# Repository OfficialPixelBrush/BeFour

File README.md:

# BeFour
The BeFour/B4/Be4 is a simplistic 4-Bit, TTL Processor, largely inspired by the Zilog Z80 and similar architectures of the late-1970s and early-1980s, just in 4-Bit.

# Goal
It's main idea is simple. How basic can I make an instruction set, while still making it somewhat useful?
This question arose out of need. I was originally trying to make a Diode-Transistor Logic Computer entirely from Scratch, which was meant to be 4-Bit too. However, planning that monstrocity became too difficult for my current skill-set, so I decided to try anew. My main goal not being an impressive instruction set, but something simple that won't require heaps of individual Diodes and Transistors. This is also why I'll be sticking with bog-standard TTL Chips for this project.

# Architecture
This Processor is entirely 4-Bit, aside from the Address Bus, which is 8-Bit.
This allows for Addressing of up to 256 Bytes of Memory, at least as a Program. The Processor is only capable of reading a 4-Bit address for RAM access, limiting it's Memory on that front to only 16 Bytes.

For more information about the Architecture, Instruction Set, Memory Map, et cetera, please [visit the Wiki page](https://github.com/OfficialPixelBrush/BeFour/wiki).

# Emulator
The provide Emulator is accurate enough for most simple Programs, and can be compiled easily with gcc.
Pre-built Binaries can usually be found in the Releases section, although these may not always be up-to-date.

## How to use
The emulator takes two parameters. The first is the filename of whichever Binary file it's supposed to execute. The second is how many instructions it'll execute before stopping. By default, this is -1, meaning it'll stop right away.

### Windows
To execute the provided Fibonacci Program, for example, one could use `.\b4emu.exe ..\software\fibo.bin 50` to execute the Fibbonaci Program for 50 Instructions.

### Linux
Similar to Windows, just different formatting:
`./b4emu ../software/fibo.bin 50`
Outside of that, make sure the binary is set to be executable.
`chmod +x b4emu`

## Binaries
You can find all Releases in the [Releases Section](https://github.com/OfficialPixelBrush/BeFour/releases).

# License
It's been difficult finding a proper license for this thus far, especially because I don't see why anyone'd want to do much with this thing.
It's my processor, feel free to be inspired by it, but don't steal it, and don't use it commercially. I'll probably replace this with a proper license sometime soon, but if you have any deeper questions, just shoot me a message via an Issue or something.

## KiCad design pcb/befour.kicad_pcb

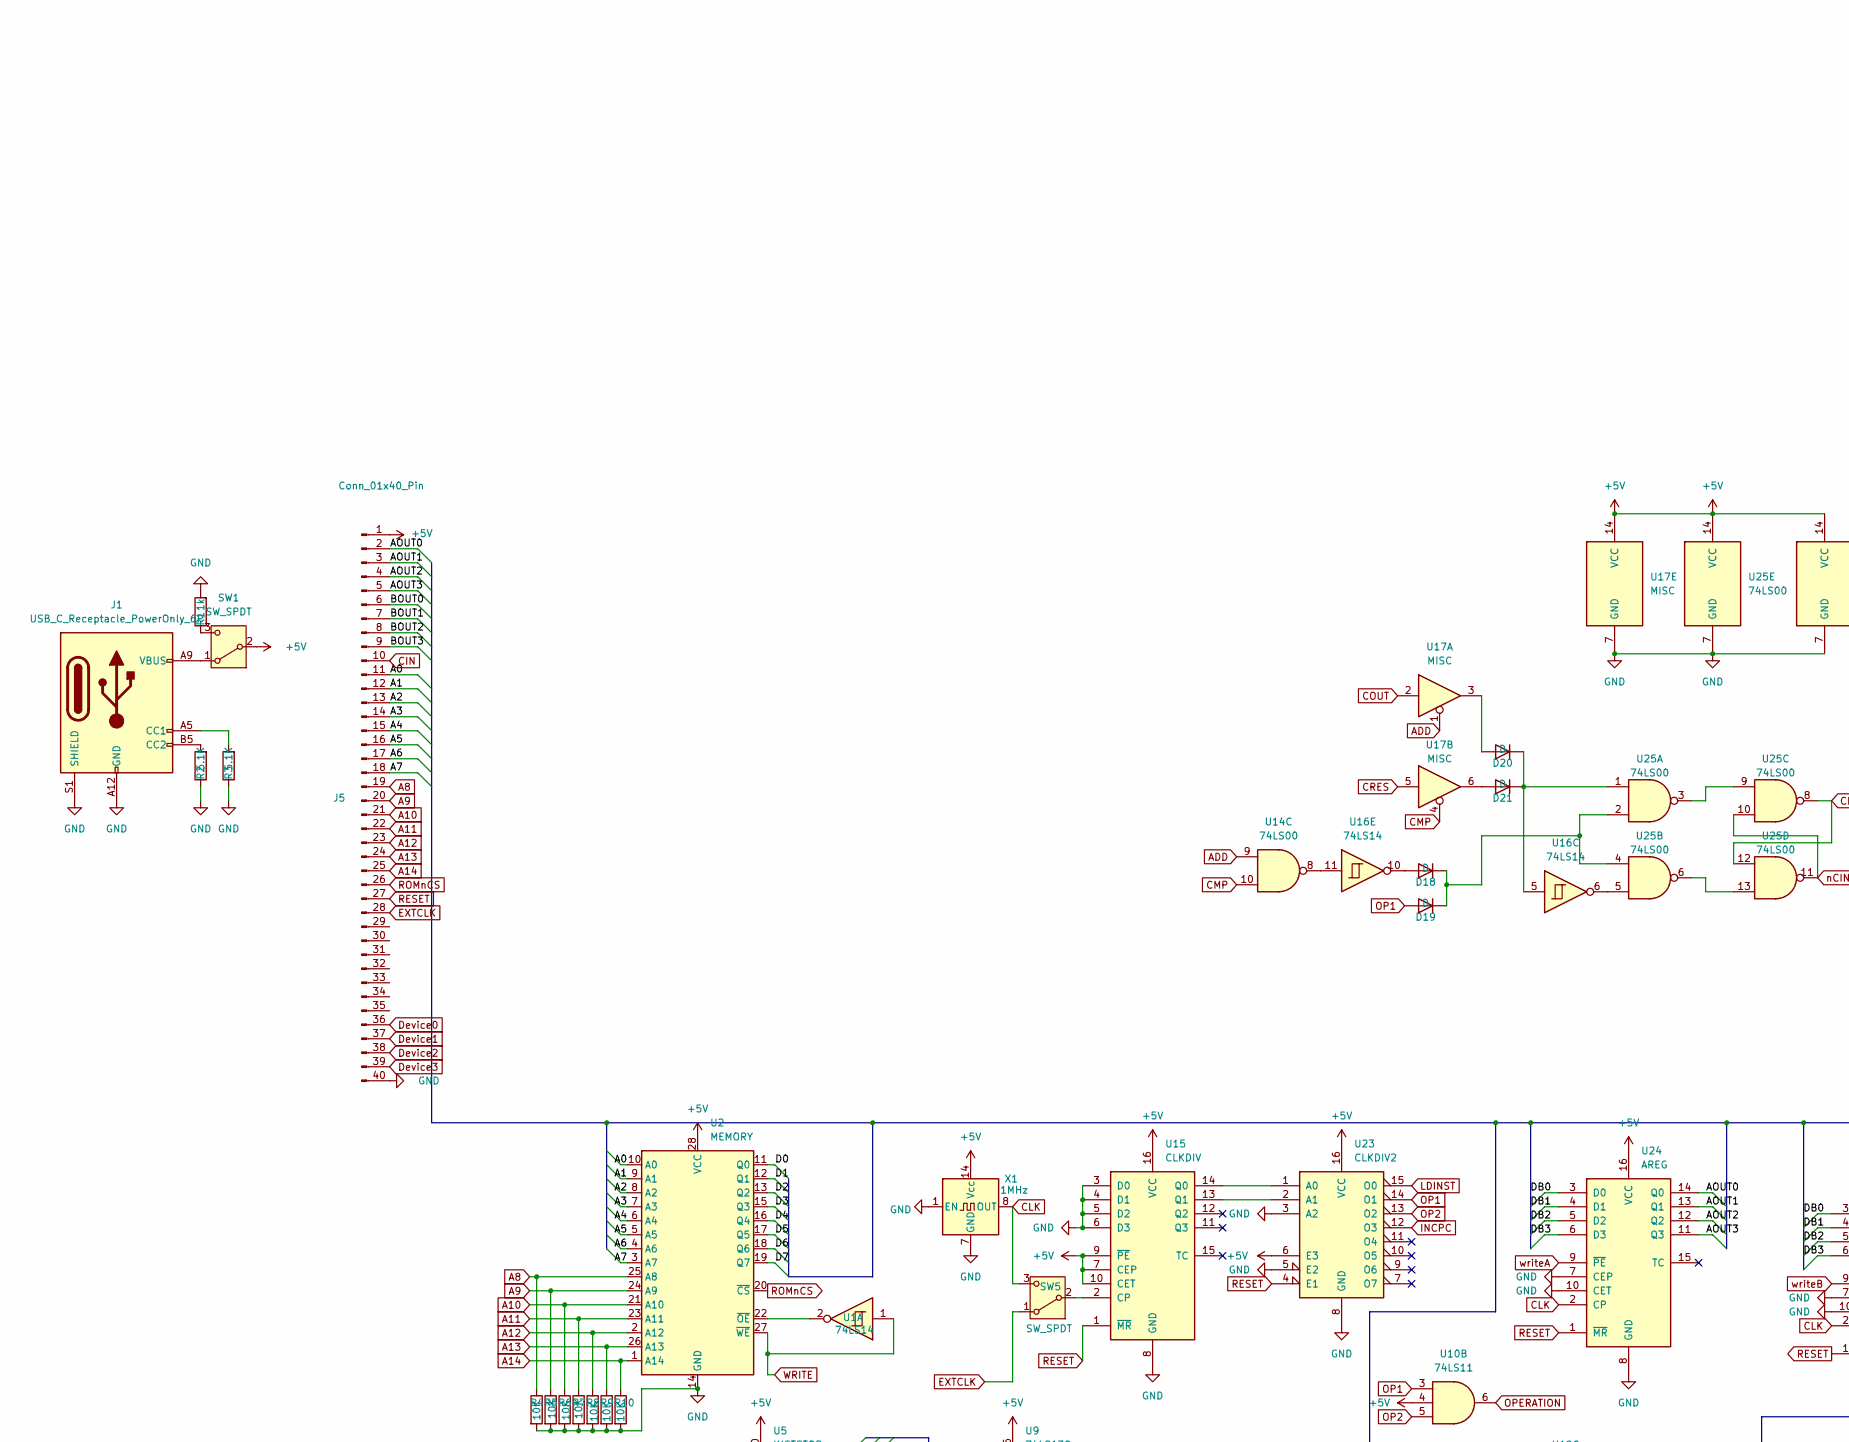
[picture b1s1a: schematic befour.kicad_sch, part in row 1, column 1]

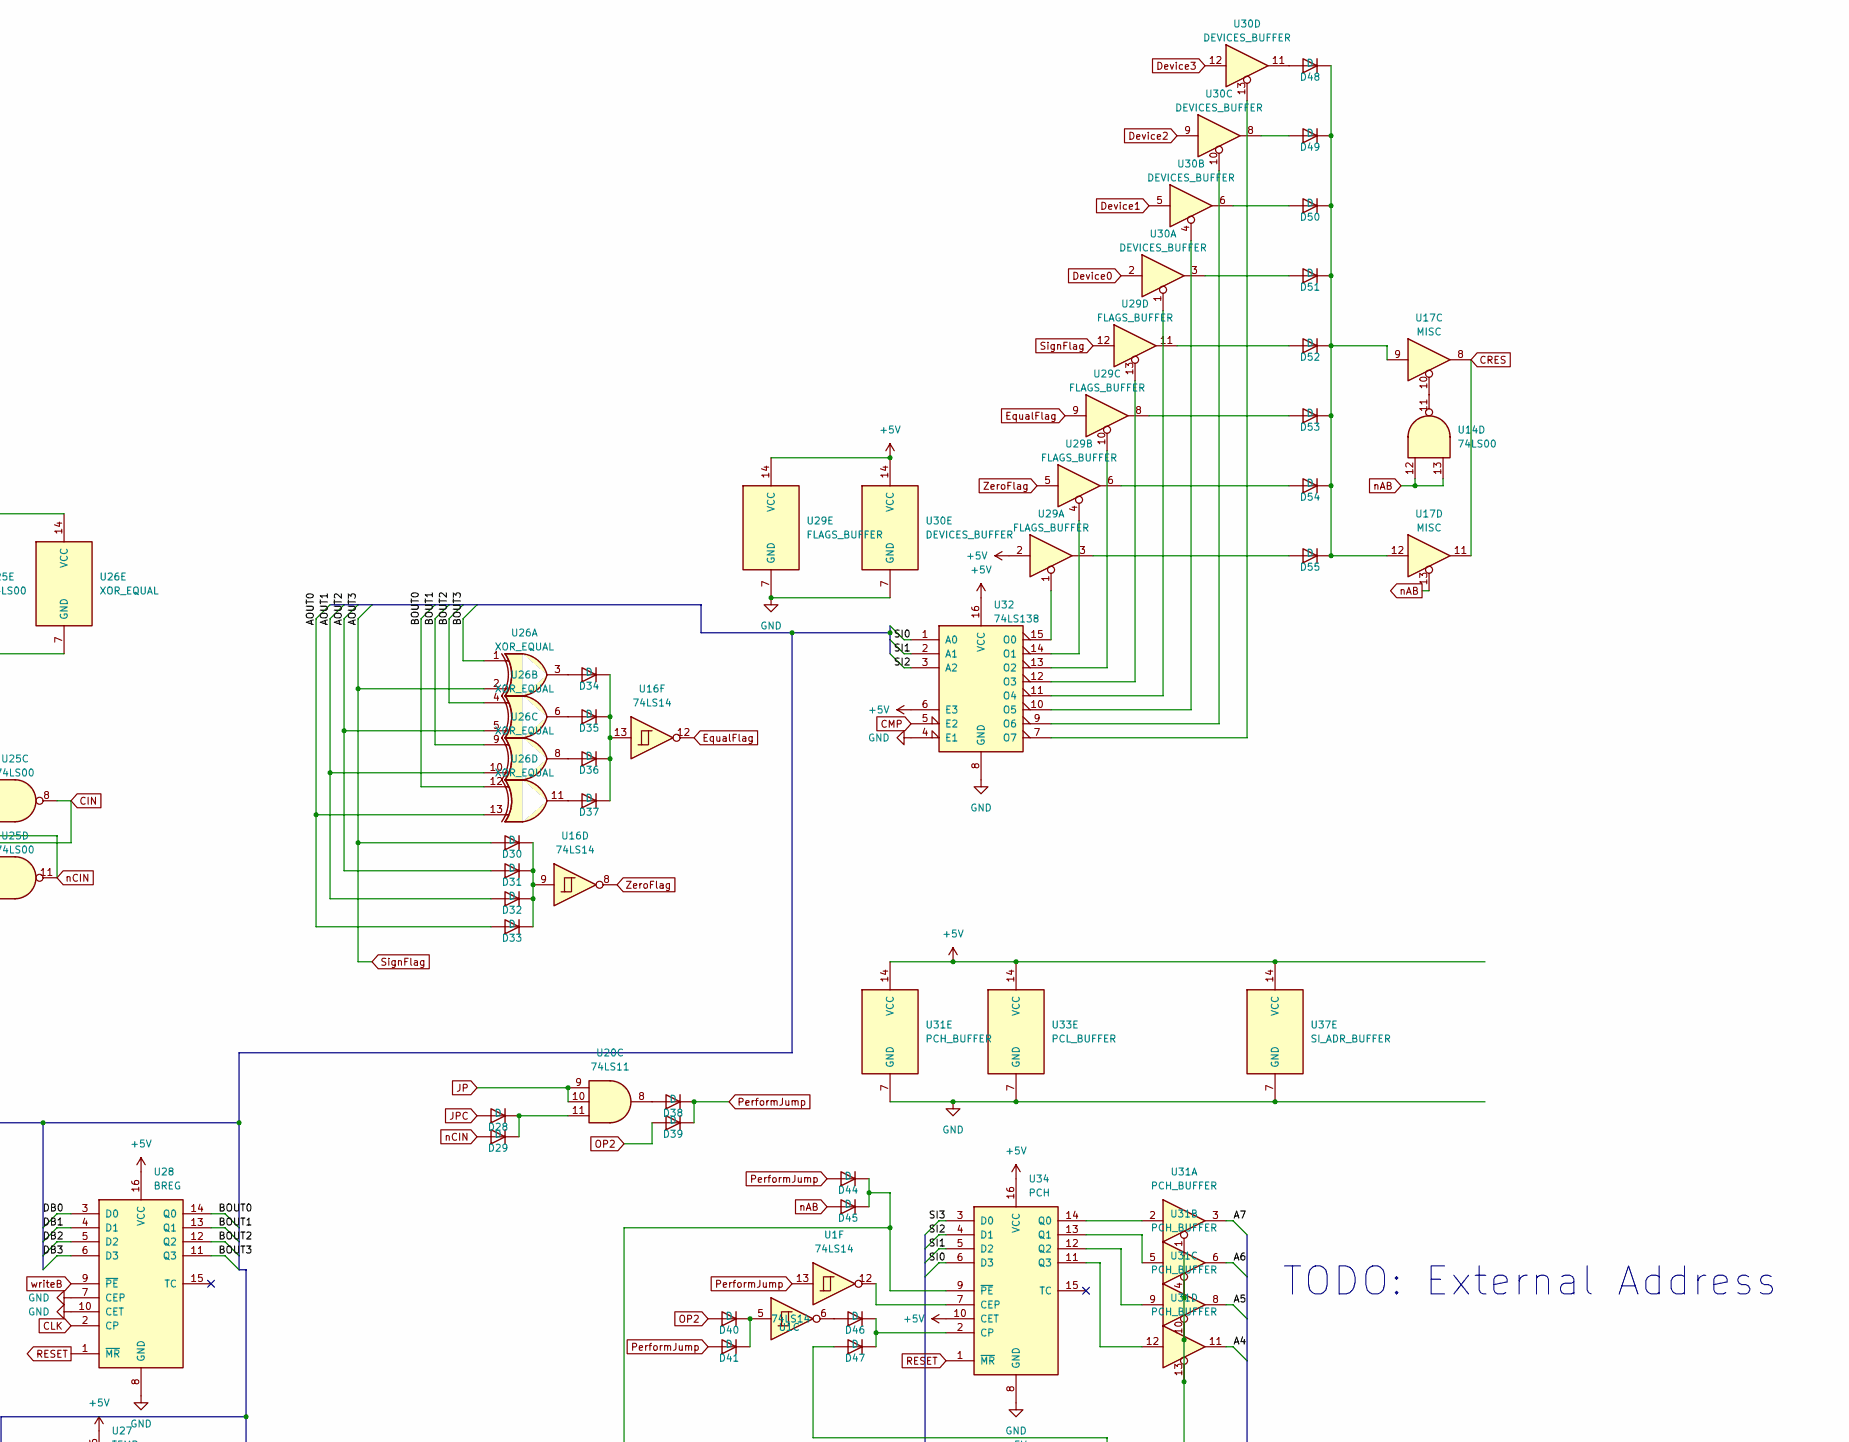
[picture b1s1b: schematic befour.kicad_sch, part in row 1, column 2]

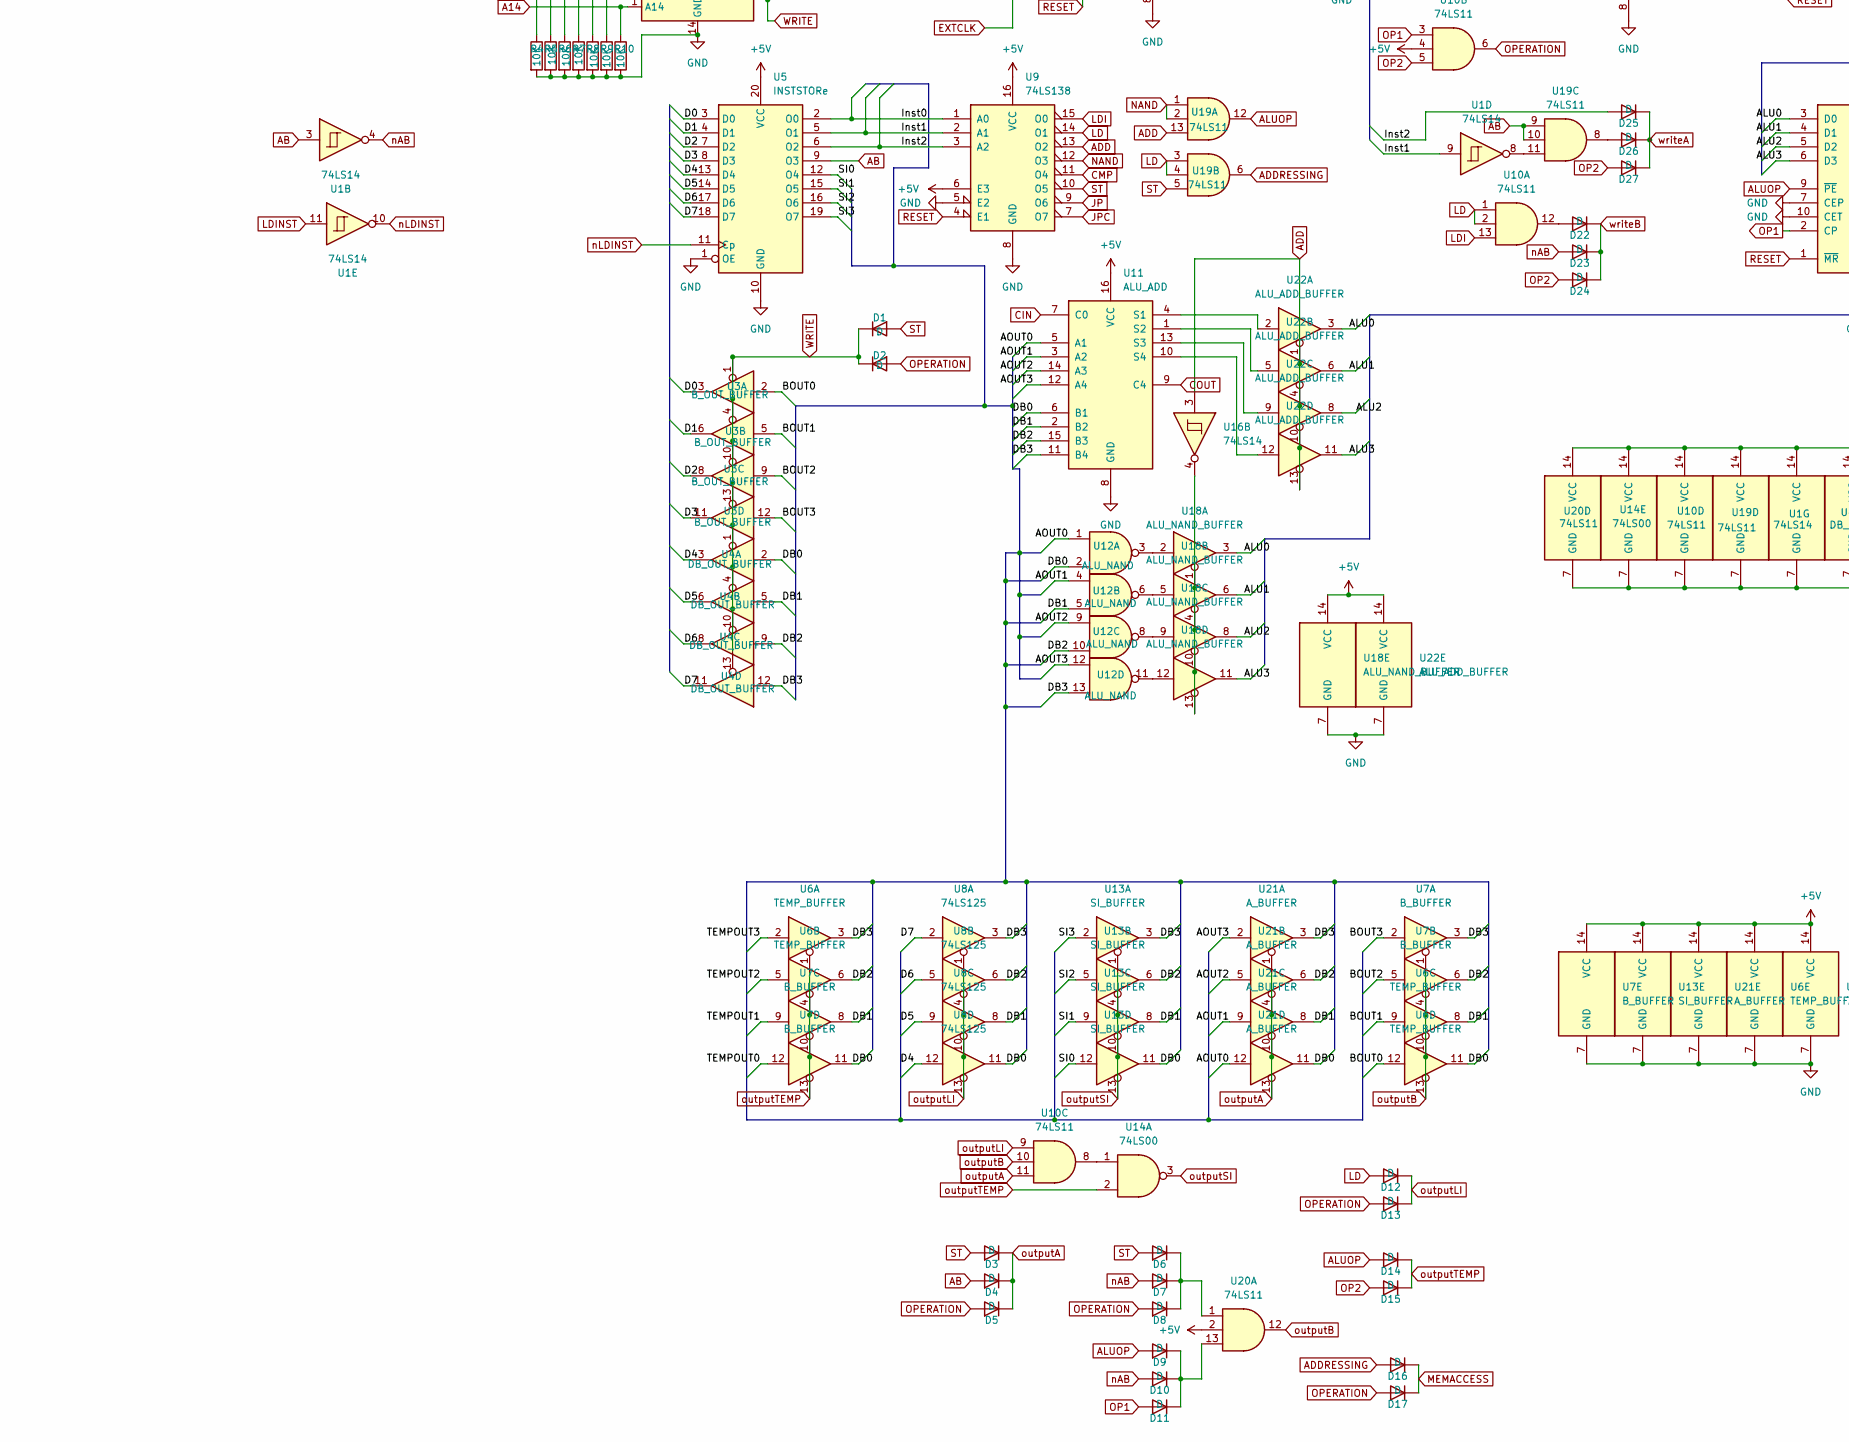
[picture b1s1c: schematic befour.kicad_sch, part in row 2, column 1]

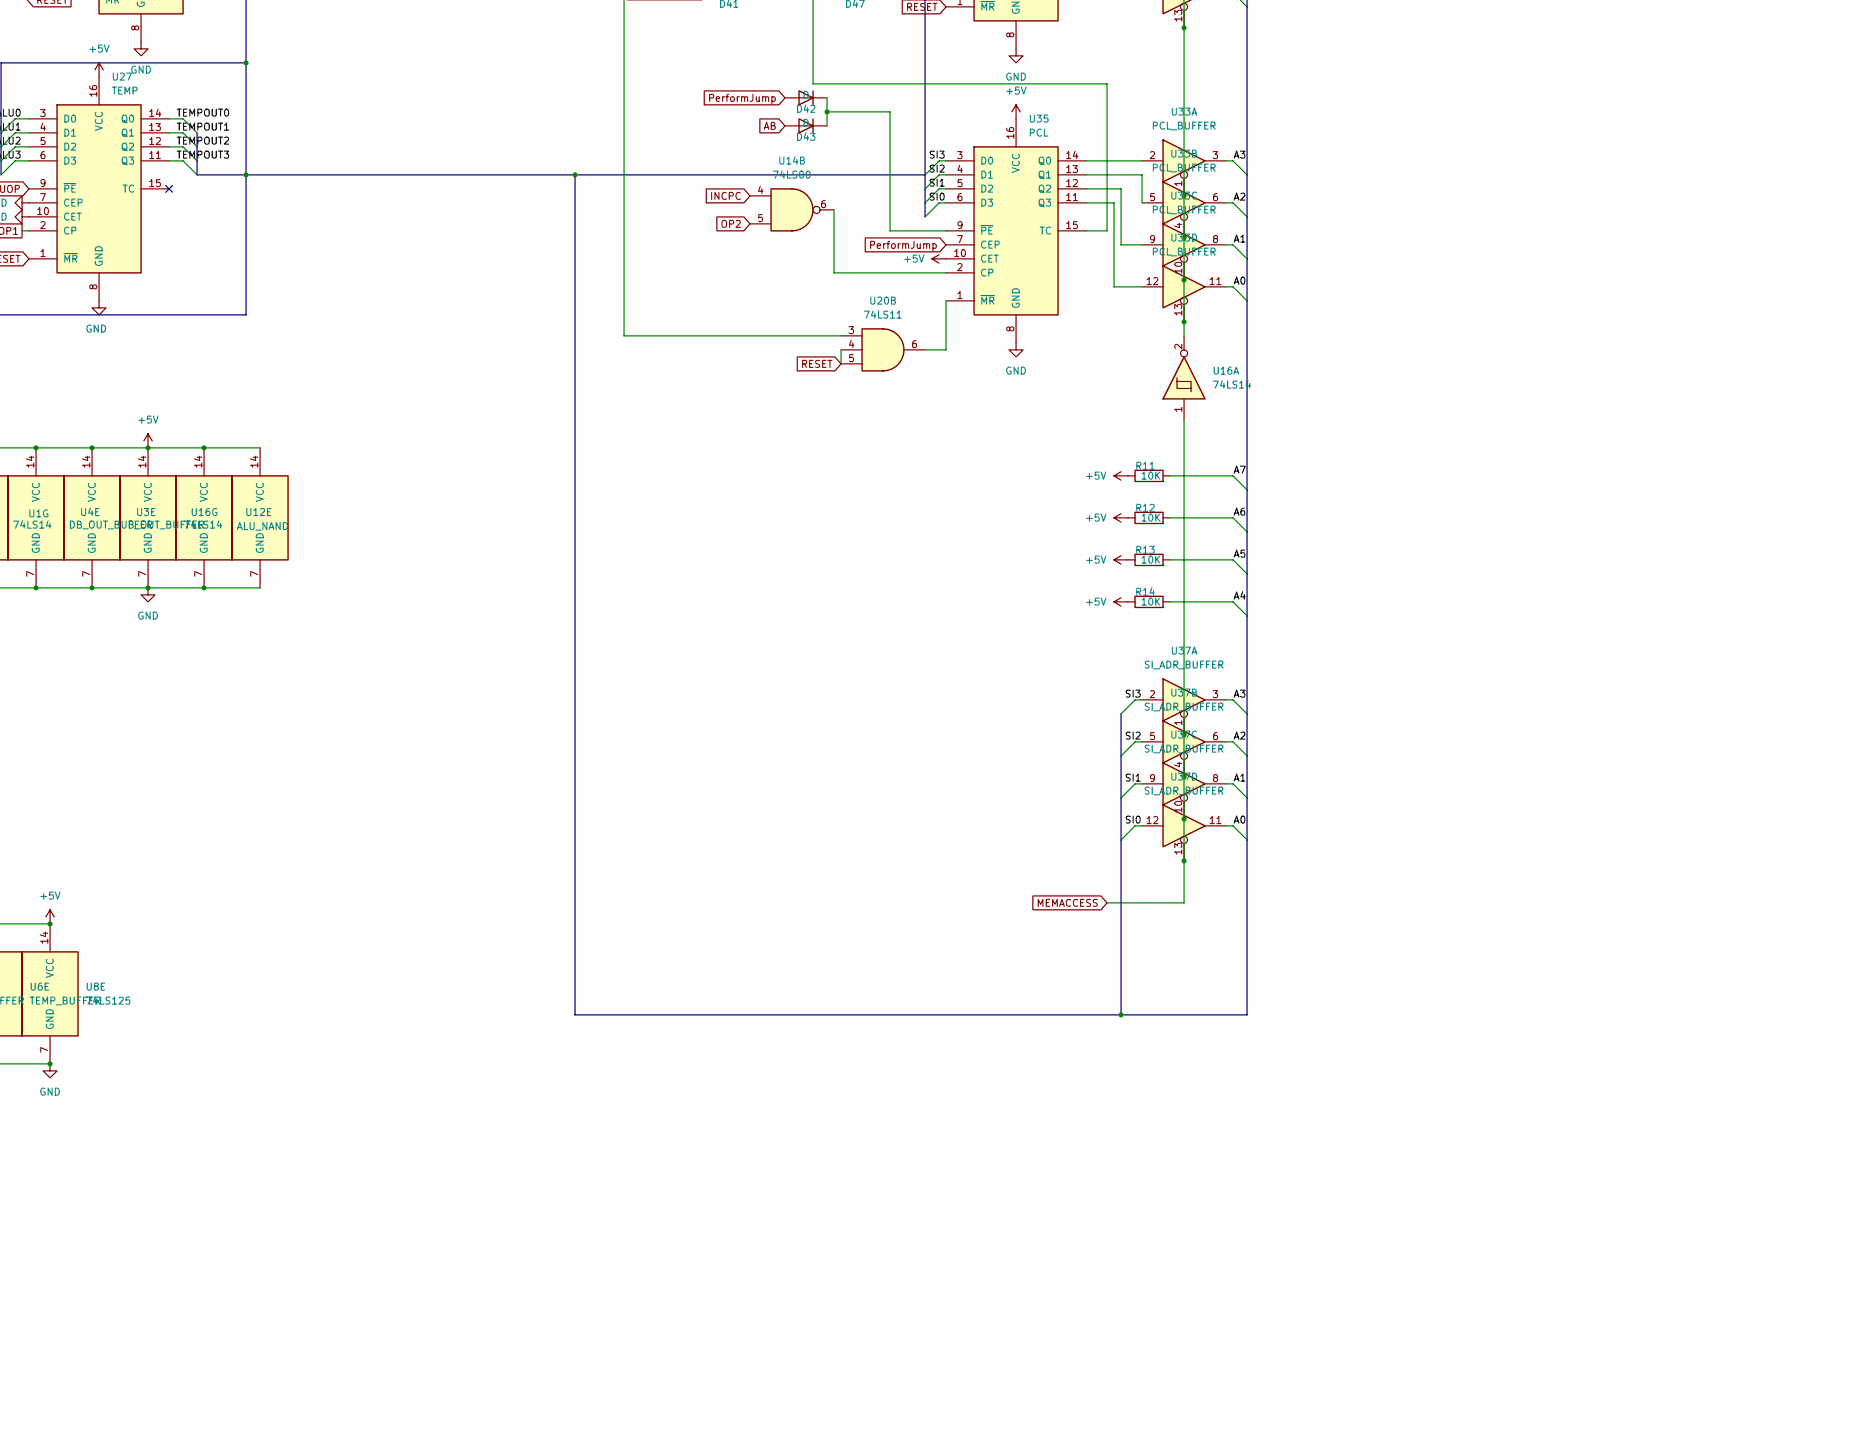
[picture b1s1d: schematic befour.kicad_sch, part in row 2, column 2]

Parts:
D1, D2, D3, D4, D5, D6, D7, D8, D9, D10, D11, D12, D13, D14, D15, D16, D17, D18, D19, D20, D21, D22, D23, D24, D25, D26, D27, D28, D29, D30, D31, D32, D33, D34, D35, D36, D37, D38, D39, D40, D41, D42, D43, D44, D45, D46, D47, D48, D49, D50, D51, D52, D53, D54, D55: D; D_DO-35_SOD27_P2.54mm_Vertical_KathodeUp
J1: USB_C_Receptacle_PowerOnly_6P; USB_C_Receptacle_GCT_USB4125-xx-x_6P_TopMnt_Horizontal
J5: Conn_01x40_Pin; PinHeader_1x40_P2.54mm_Horizontal
R1: 1k; R_Axial_DIN0309_L9.0mm_D3.2mm_P2.54mm_Vertical
R2, R3: 5.1K; R_Axial_DIN0309_L9.0mm_D3.2mm_P2.54mm_Vertical
R4, R5, R6, R7, R8, R9, R10, R11, R12, R13, R14: 10K; R_Axial_DIN0309_L9.0mm_D3.2mm_P2.54mm_Vertical
SW1: SW_SPDT; PinHeader_1x03_P2.54mm_Vertical
SW5: SW_SPDT; SW_Slide_SPDT_Straight_CK_OS102011MS2Q
U1, U16: 74LS14; DIP-14_W7.62mm_Socket
U2: MEMORY; DIP-28_W15.24mm
U3: B_OUT_BUFFER; DIP-14_W7.62mm_Socket
U4: DB_OUT_BUFFER; DIP-14_W7.62mm_Socket
U5: INSTSTORe; DIP-20_W7.62mm_Socket
U6: TEMP_BUFFER; DIP-14_W7.62mm_Socket
U7: B_BUFFER; DIP-14_W7.62mm_Socket
U8: 74LS125; DIP-14_W7.62mm_Socket
U9, U32: 74LS138; DIP-16_W7.62mm_Socket
U10, U19, U20: 74LS11; DIP-14_W7.62mm_Socket
U11: ALU_ADD; DIP-16_W7.62mm_Socket
U12: ALU_NAND; DIP-14_W7.62mm_Socket
U13: SI_BUFFER; DIP-14_W7.62mm_Socket
U14, U25: 74LS00; DIP-14_W7.62mm_Socket
U15: CLKDIV; DIP-16_W7.62mm_Socket
U17: MISC; DIP-14_W7.62mm_Socket
U18: ALU_NAND_BUFFER; DIP-14_W7.62mm_Socket
U21: A_BUFFER; DIP-14_W7.62mm_Socket
U22: ALU_ADD_BUFFER; DIP-14_W7.62mm_Socket
U23: CLKDIV2; DIP-16_W7.62mm_Socket
U24: AREG; DIP-16_W7.62mm_Socket
U26: XOR_EQUAL; DIP-14_W7.62mm_Socket
U27: TEMP; DIP-16_W7.62mm_Socket
U28: BREG; DIP-16_W7.62mm_Socket
U29: FLAGS_BUFFER; DIP-14_W7.62mm_Socket
U30: DEVICES_BUFFER; DIP-14_W7.62mm_Socket
U31: PCH_BUFFER; DIP-14_W7.62mm_Socket
U33: PCL_BUFFER; DIP-14_W7.62mm_Socket
U34: PCH; DIP-16_W7.62mm_Socket
U35: PCL; DIP-16_W7.62mm_Socket
U37: SI_ADR_BUFFER; DIP-14_W7.62mm_Socket
X1: 1MHz; Oscillator_DIP-14

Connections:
+5V: J5.1, R11.1, R12.1, R13.1, R14.1, SW1.2 (B), U1.14 (VCC), U2.28 (VCC), U3.14 (VCC), U4.14 (VCC), U5.20 (VCC), U6.14 (VCC), U7.14 (VCC), U8.14 (VCC), U9.6 (E3), U9.16 (VCC), U10.4, U10.14 (VCC), U11.16 (VCC), U12.14 (VCC), U13.14 (VCC), U14.14 (VCC), U15.7 (CEP), U15.9 (~PE), U15.10 (CET), U15.16 (VCC), U16.14 (VCC), U17.14 (VCC), U18.14 (VCC), U19.14 (VCC), U20.2, U20.14 (VCC), U21.14 (VCC), U22.14 (VCC), U23.6 (E3), U23.16 (VCC), U24.16 (VCC), U25.14 (VCC), U26.14 (VCC), U27.16 (VCC), U28.16 (VCC), U29.2, U29.14 (VCC), U30.14 (VCC), U31.14 (VCC), U32.6 (E3), U32.16 (VCC), U33.14 (VCC), U34.10 (CET), U34.16 (VCC), U35.10 (CET), U35.16 (VCC), U37.14 (VCC), X1.14 (Vcc)
/A0: J5.11, U2.10 (A0), U33.11, U37.11
/A1: J5.12, U2.9 (A1), U33.8, U37.8
/A2: J5.13, U2.8 (A2), U33.6, U37.6
/A3: J5.14, U2.7 (A3), U33.3, U37.3
/A4: J5.15, R14.2, U2.6 (A4), U31.11
/A5: J5.16, R13.2, U2.5 (A5), U31.8
/A6: J5.17, R12.2, U2.4 (A6), U31.6
/A7: J5.18, R11.2, U2.3 (A7), U31.3
/ALU0: U18.3, U22.3, U27.3 (D0)
/ALU1: U18.6, U22.6, U27.4 (D1)
/ALU2: U18.8, U22.8, U27.5 (D2)
/ALU3: U18.11, U22.11, U27.6 (D3)
/AOUT0: D33.2 (A), J5.2, U11.5 (A1), U12.1, U21.12, U24.14 (Q0), U26.13
/AOUT1: D32.2 (A), J5.3, U11.3 (A2), U12.4, U21.9, U24.13 (Q1), U26.10
/AOUT2: D31.2 (A), J5.4, U11.14 (A3), U12.9, U21.5, U24.12 (Q2), U26.5
/BOUT0: J5.6, U3.2, U6.12, U26.12, U28.14 (Q0)
/BOUT1: J5.7, U3.5, U6.9, U26.9, U28.13 (Q1)
/BOUT2: J5.8, U3.9, U7.5, U26.4, U28.12 (Q2)
/BOUT3: J5.9, U3.12, U7.2, U26.1, U28.11 (Q3)
/D0: U2.11 (Q0), U3.3, U5.3 (D0)
/D1: U2.12 (Q1), U3.6, U5.4 (D1)
/D2: U2.13 (Q2), U3.8, U5.7 (D2)
/D3: U2.15 (Q3), U3.11, U5.8 (D3)
/D4: U2.16 (Q4), U4.3, U5.13 (D4), U8.12
/D5: U2.17 (Q5), U4.6, U5.14 (D5), U8.9
/D6: U2.18 (Q6), U4.8, U5.17 (D6), U8.5
/D7: U2.19 (Q7), U4.11, U5.18 (D7), U8.2
/DB0: U4.2, U6.11, U7.11, U8.11, U11.6 (B1), U12.2, U13.11, U21.11, U24.3 (D0), U28.3 (D0)
/DB1: U4.5, U6.8, U7.8, U8.8, U11.2 (B2), U12.5, U13.8, U21.8, U24.4 (D1), U28.4 (D1)
/DB2: U4.9, U6.6, U7.6, U8.6, U11.15 (B3), U12.10, U13.6, U21.6, U24.5 (D2), U28.5 (D2)
/DB3: U4.12, U6.3, U7.3, U8.3, U11.11 (B4), U12.13, U13.3, U21.3, U24.6 (D3), U28.6 (D3)
/Inst0: U5.2 (O0), U9.1 (A0)
/Inst1: U1.9, U5.5 (O1), U9.2 (A1)
/Inst2: D25.2 (A), U5.6 (O2), U9.3 (A2)
/SI0: U5.12 (O4), U13.12, U32.1 (A0), U34.6 (D3), U35.6 (D3), U37.12
/SI1: U5.15 (O5), U13.9, U32.2 (A1), U34.5 (D2), U35.5 (D2), U37.9
/SI2: U5.16 (O6), U13.5, U32.3 (A2), U34.4 (D1), U35.4 (D1), U37.5
/SI3: U5.19 (O7), U13.2, U34.3 (D0), U35.3 (D0), U37.2
/TEMPOUT0: U7.12, U27.14 (Q0)
/TEMPOUT1: U7.9, U27.13 (Q1)
/TEMPOUT2: U6.5, U27.12 (Q2)
/TEMPOUT3: U6.2, U27.11 (Q3)
A8: J5.19, R4.1, U2.25 (A8)
A9: J5.20, R5.1, U2.24 (A9)
A10: J5.21, R6.1, U2.21 (A10)
A11: J5.22, R7.1, U2.23 (A11)
A12: J5.23, R8.1, U2.2 (A12)
A13: J5.24, R9.1, U2.26 (A13)
A14: J5.25, R10.1, U2.1 (A14)
AB: D4.2 (A), D43.2 (A), U1.3, U5.9 (O3), U19.9, U19.10
ADD: U9.13 (O2), U14.9, U16.3, U17.1, U19.13, U22.1, U22.4, U22.10, U22.13
ADDRESSING: D16.2 (A), U19.6
ALUOP: D9.2 (A), D14.2 (A), U19.12, U27.9 (~PE)
CIN: J5.10, U11.7 (C0), U25.8, U25.12
CLK: SW5.3 (C), U24.2 (CP), U28.2 (CP), X1.8 (OUT)
CMP: U9.11 (O4), U14.10, U17.4, U32.5 (E2)
COUT: U11.9 (C4), U17.2
CRES: U17.5, U17.8, U17.11
Device0: J5.36, U30.2
Device1: J5.37, U30.5
Device2: J5.38, U30.9
Device3: J5.39, U30.12
EXTCLK: J5.28, SW5.1 (A)
EqualFlag: U16.12, U29.9
GND: J1.A12 (GND), J1.B12 (GND), J1.S1 (SHIELD), J5.40, R1.2, R2.1, R3.1, R4.2, R5.2, R6.2, R7.2, R8.2, R9.2, R10.2, U1.7 (GND), U2.14 (GND), U3.7 (GND), U4.7 (GND), U5.1 (OE), U5.10 (GND), U6.7 (GND), U7.7 (GND), U8.7 (GND), U9.5 (E2), U9.8 (GND), U10.7 (GND), U11.8 (GND), U12.7 (GND), U13.7 (GND), U14.7 (GND), U15.3 (D0), U15.4 (D1), U15.5 (D2), U15.6 (D3), U15.8 (GND), U16.7 (GND), U17.7 (GND), U18.7 (GND), U19.7 (GND), U20.7 (GND), U21.7 (GND), U22.7 (GND), U23.3 (A2), U23.5 (E2), U23.8 (GND), U24.7 (CEP), U24.8 (GND), U24.10 (CET), U25.7 (GND), U26.7 (GND), U27.7 (CEP), U27.8 (GND), U27.10 (CET), U28.7 (CEP), U28.8 (GND), U28.10 (CET), U29.7 (GND), U30.7 (GND), U31.7 (GND), U32.4 (E1), U32.8 (GND), U33.7 (GND), U34.8 (GND), U35.8 (GND), U37.7 (GND), X1.1 (EN), X1.7 (GND)
INCPC: U14.4, U23.12 (O3)
JP: U9.9 (O6), U20.9, U20.10
JPC: D28.2 (A), U9.7 (O7)
LD: D12.2 (A), U9.14 (O1), U10.1, U10.2, U19.3, U19.4
LDI: U9.15 (O0), U10.13
LDINST: U1.11, U23.15 (O0)
MEMACCESS: D16.1 (K), D17.1 (K), U16.1, U37.1, U37.4, U37.10, U37.13
NAND: U9.12 (O3), U19.1, U19.2
unnamed: D6.1 (K), D7.1 (K), D8.1 (K), U20.1
unnamed: D9.1 (K), D10.1 (K), D11.1 (K), U20.13
unnamed: D18.2 (A), U16.10
unnamed: D18.1 (K), D19.1 (K), U25.2, U25.4
unnamed: D20.2 (A), U17.3
unnamed: D20.1 (K), D21.1 (K), U16.5, U25.1
unnamed: D21.2 (A), U17.6
unnamed: D22.2 (A), U10.12
unnamed: D26.2 (A), U19.8
unnamed: D28.1 (K), D29.1 (K), U20.11
unnamed: D30.1 (K), D31.1 (K), D32.1 (K), D33.1 (K), U16.9
unnamed: D34.2 (A), U26.3
unnamed: D34.1 (K), D35.1 (K), D36.1 (K), D37.1 (K), U16.13
unnamed: D35.2 (A), U26.6
unnamed: D36.2 (A), U26.8
unnamed: D37.2 (A), U26.11
unnamed: D38.2 (A), U20.8
unnamed: D40.1 (K), D41.1 (K), U1.5
unnamed: D42.1 (K), D43.1 (K), U35.9 (~PE)
unnamed: D44.1 (K), D45.1 (K), U20.3, U34.9 (~PE)
unnamed: D46.2 (A), U1.6
unnamed: D46.1 (K), D47.1 (K), U34.2 (CP)
unnamed: D47.2 (A), U35.15 (TC)
unnamed: D48.2 (A), U30.11
unnamed: D48.1 (K), D49.1 (K), D50.1 (K), D51.1 (K), D52.1 (K), D53.1 (K), D54.1 (K), D55.1 (K), U17.9, U17.12
unnamed: D49.2 (A), U30.8
unnamed: D50.2 (A), U30.6
unnamed: D51.2 (A), U30.3
unnamed: D52.2 (A), U29.11
unnamed: D53.2 (A), U29.8
unnamed: D54.2 (A), U29.6
unnamed: D55.2 (A), U29.3
unnamed: J1.A5 (CC1), R3.2
unnamed: J1.B5 (CC2), R2.2
unnamed: J1.A9 (VBUS), J1.B9 (VBUS), SW1.1 (A)
unnamed: R1.1, SW1.3 (C)
unnamed: SW5.2 (B), U15.2 (CP)
unnamed: U1.8, U19.11
unnamed: U1.2, U2.22 (~OE)
unnamed: U10.8, U14.1
unnamed: U11.4 (S1), U22.2
unnamed: U11.1 (S2), U22.5
unnamed: U11.13 (S3), U22.9
unnamed: U11.10 (S4), U22.12
unnamed: U12.3, U18.2
unnamed: U12.6, U18.5
unnamed: U12.8, U18.9
unnamed: U12.11, U18.12
unnamed: U14.8, U16.11
unnamed: U14.11, U17.10
unnamed: U15.14 (Q0), U23.1 (A0)
unnamed: U15.13 (Q1), U23.2 (A1)
unnamed: U16.2, U31.1, U31.4, U31.10, U31.13, U33.1, U33.4, U33.10, U33.13
unnamed: U16.4, U18.1, U18.4, U18.10, U18.13
unnamed: U16.6, U25.5
unnamed: U25.3, U25.9
unnamed: U25.6, U25.13
unnamed: U29.1, U32.15 (O0)
unnamed: U29.4, U32.14 (O1)
unnamed: U29.10, U32.13 (O2)
unnamed: U29.13, U32.12 (O3)
unnamed: U30.1, U32.11 (O4)
unnamed: U30.4, U32.10 (O5)
unnamed: U30.10, U32.9 (O6)
unnamed: U30.13, U32.7 (O7)
unnamed: U1.12, U34.7 (CEP)
unnamed: U31.2, U34.14 (Q0)
unnamed: U31.5, U34.13 (Q1)
unnamed: U31.9, U34.12 (Q2)
unnamed: U31.12, U34.11 (Q3)
unnamed: U14.6, U35.2 (CP)
unnamed: U33.2, U35.14 (Q0)
unnamed: U33.5, U35.13 (Q1)
unnamed: U33.9, U35.12 (Q2)
unnamed: U33.12, U35.11 (Q3)
unnamed: U20.6, U35.1 (~MR)
OP1: D11.2 (A), D19.2 (A), U10.3, U23.14 (O1), U27.2 (CP)
OP2: D15.2 (A), D24.2 (A), D27.2 (A), D39.2 (A), D40.2 (A), U10.5, U14.5, U23.13 (O2)
OPERATION: D2.2 (A), D5.2 (A), D8.2 (A), D13.2 (A), D17.2 (A), U10.6
PerformJump: D38.1 (K), D39.1 (K), D41.2 (A), D42.2 (A), D44.2 (A), U1.13, U35.7 (CEP)
RESET: J5.27, U9.4 (E1), U15.1 (~MR), U20.4, U20.5, U23.4 (E1), U24.1 (~MR), U27.1 (~MR), U28.1 (~MR), U34.1 (~MR)
ROMnCS: J5.26, U2.20 (~CS)
ST: D1.2 (A), D3.2 (A), D6.2 (A), U9.10 (O5), U19.5
SignFlag: D30.2 (A), J5.5, U11.12 (A4), U12.12, U21.2, U24.11 (Q3), U26.2, U29.12
WRITE: D1.1 (K), D2.1 (K), U1.1, U2.27 (~WE), U3.1, U3.4, U3.10, U3.13, U4.1, U4.4, U4.10, U4.13
ZeroFlag: U16.8, U29.5
nAB: D7.2 (A), D10.2 (A), D23.2 (A), D45.2 (A), U1.4, U14.12, U14.13, U17.13
nCIN: D29.2 (A), U25.10, U25.11
nLDINST: U1.10, U5.11 (Cp)
outputA: D3.1 (K), D4.1 (K), D5.1 (K), U10.11, U21.1, U21.4, U21.10, U21.13
outputB: U6.10, U6.13, U7.1, U7.4, U10.10, U20.12
outputLI: D12.1 (K), D13.1 (K), U8.1, U8.4, U8.10, U8.13, U10.9
outputSI: U13.1, U13.4, U13.10, U13.13, U14.3
outputTEMP: D14.1 (K), D15.1 (K), U6.1, U6.4, U7.10, U7.13, U14.2
writeA: D25.1 (K), D26.1 (K), D27.1 (K), U24.9 (~PE)
writeB: D22.1 (K), D23.1 (K), D24.1 (K), U28.9 (~PE)

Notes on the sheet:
TODO: External Address

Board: 2 copper layers, 110 parts (0 on the bottom side), 170 nets, no tracks yet.

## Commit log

2024-02-14 some stuff works
2024-02-14 halfway there
2024-02-15 this is pain
2024-02-15 idk man
2024-02-19 idk, make it work
2024-02-19 getting there
2024-02-19 finished
2024-02-19 tweaks
2024-02-19 globalRename
2024-02-20 Load works now, and the emulator is more helpful
2024-02-20 tweak
2024-02-20 emulator updated
2024-02-22 changed carry to conditional
2024-02-22 changes.
2024-02-22 jumps seem to work
2024-02-25 CMP section
2024-02-26 IT WORKS
2024-02-26 Test Program
2024-02-27 test
2024-02-27 added kicad pcb
2024-02-27 Update README.md
    + Link to Releases page
    + Tutorial for running with parameters
2024-02-27 Update README.md
    tweak
2024-02-27 Update README.md
    undo tweak
2024-02-29 started work on schematic
2024-03-02 more pcb work
2024-03-03 the Schematic is complete.
2024-03-04 schematic tweaks
2024-03-06 mandelbrot attempt
2024-03-15 god I want this thing to have a 12-bit address bus
